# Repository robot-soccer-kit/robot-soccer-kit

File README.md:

# Robot Soccer Kit

## Presentation

* [YouTube demonstration video](https://www.youtube.com/watch?v=4NFXbaom7YQ)
* [Documentation](https://robot-soccer-kit.github.io)

The changes of each version are listed in [CHANGELOG.md](CHANGELOG.md).

## Installation

Python 3.9 or newer is required. The Game Controller (interface, vision, referee) needs the `gc`
extra:

```
pip install -U "robot-soccer-kit[gc]"
```

Only the client (to program the robots from Python) is installed without the extra:
`pip install -U robot-soccer-kit`.

**Windows**: double-click `game-controller.bat`. It installs (or updates) the package and starts
the Game Controller. It uses the `py` launcher, installed with Python from
[python.org](https://www.python.org/downloads/) (the Python of the Microsoft Store doesn't have
it).

## Game Controller

```
python -m rsk.game_controller
```

The interface opens in the browser at http://127.0.0.1:7070. Options:

| Option | Effect |
|---|---|
| `-s`, `--simulated` | Simulated robots and ball, no camera needed |
| `-c`, `--competition` | Competition mode |
| `-S URL`, `--scheduler URL` | Games of a scheduler |
| `-R FILE`, `--replay FILE` | Replay a recorded game |
| `--ip IP`, `-p PORT` | Address and port of the interface |
| `-r`, `--reset` | Reset the configuration file |
| `-d`, `--dry` | Start and stop without serving the interface (installation check) |

The configuration (robots, cameras, settings) is saved in `config.json`. Robots are not saved in
simulation and replay modes, so a simulated run doesn't replace the real robots. Recorded games
are written in `rsk_recorder/`, in the directory where the Game Controller is started.

### Vision

In the **Vision** tab:

* **Camera and resolution**: a preview of the chosen camera is shown before the vision starts.
  On Linux, the cameras are listed with their names, and only the resolutions they can give
  are proposed (with their frame rate).
* **Settings per camera**: the camera settings and the lens calibration are saved for each
  camera; changing the camera brings back its settings. A camera used for the first time gets
  its own default image settings (when known, Linux).
* **Auto**: sets the image settings to the defaults of the camera, then searches the exposure
  (brightest parts of the field bright but not saturated, or a medium brightness when the
  field is not calibrated yet: run it again once the four field markers are visible).
* **Auto crop**: crops the image to the field and the border around it.
* **Lights**: 50 Hz, 60 Hz or none. With 50 or 60 Hz, the exposure is a multiple of the
  flickering period of the lights, to avoid bands on the image.
* **Lens calibration** (Camera tab): see below.

The default focal (935) is the one of the recommended camera. A configuration that still has the
previous default (885) is updated, a custom focal is kept.

### Lens calibration

Wide angle lenses distort the image: without calibration, positions near the field borders can
be wrong by 1 to 2.5 cm (a few millimeters with it). The calibration measures the focal, the optical center and the
distortion with a ChArUco board (a chessboard with ArUco markers, the size doesn't matter):

1. Download the board from the *Lens calibration* card (Vision tab), print it, glue it on a
   flat rigid support.
2. Start the calibration and move the board in front of the camera: a view is captured each
   time the board is still in a new position (a green frame is shown). At least 30 views are
   needed, and all the zones of the coverage grid must be green (bring the board in the
   corners).
3. Compute, check the result (reprojection error, focal, field of view), then apply. The focal
   setting is also set to the measured focal.

The calibration is used only at the resolution it was made with. The same calibration can be
done with a command line tool:

```
python -m rsk.calibrate_camera --generate            # writes calibration_board.png
python -m rsk.calibrate_camera --camera 0            # live calibration ('q' cancels)
python -m rsk.calibrate_camera --images "views/*.png"
```

### Windows specifics

On Windows, OpenCV doesn't give the names, the resolutions nor the ranges of the settings of the
cameras:

* the cameras are listed by index, all the resolutions are proposed;
* the exposure is the log2 of the exposure time in seconds (e.g. `-7` for 1/128 s), so it can't
  follow the flickering of the lights, and the anti-flicker of the camera is not set;
* the automatic settings only search the exposure (the defaults of the camera are unknown).

## Development

The project is managed with [uv](https://docs.astral.sh/uv/):

```
uv sync --extra gc
uv run -m rsk.game_controller -s
```

### Tests

```
uv run --extra gc --group dev pytest tests
```

The test dependencies (pytest, hypothesis, playwright) are only installed with `--group dev`.
No Game Controller should be running (the tests use the ports 7557 and 7558).

* **Interface tests** (`tests/test_ui.py`) run in a headless Chrome, or Chromium installed with
  `uv run --group dev playwright install chromium`. They are skipped without a browser.
* **Tests with real cameras** (`tests/test_cameras_hardware.py`) are skipped unless
  `RSK_TEST_CAMERAS=1`. They check the listing, resolutions, preview rate, automatic settings
  and vision with the cameras plugged in (no other program should use them). They change the
  settings of the cameras (until unplugged), not the configuration file:

  ```
  # Linux / macOS
  RSK_TEST_CAMERAS=1 uv run --extra gc --group dev pytest tests/test_cameras_hardware.py -v -s
  # Windows (PowerShell)
  $env:RSK_TEST_CAMERAS=1; uv run --extra gc --group dev pytest tests/test_cameras_hardware.py -v -s
  ```

The CI runs the tests on Linux, macOS and Windows, with Python 3.9 to 3.14.

### Other commands

```
make format   # ruff format rsk/ tests/
make test     # tests
make          # build the package (python -m build)
```

## License

<br />This work is licensed under a <a rel="license" href="http://creativecommons.org/licenses/by-nc/2.0/">Creative Commons Attribution-NonCommercial 2.0 Generic License</a>.

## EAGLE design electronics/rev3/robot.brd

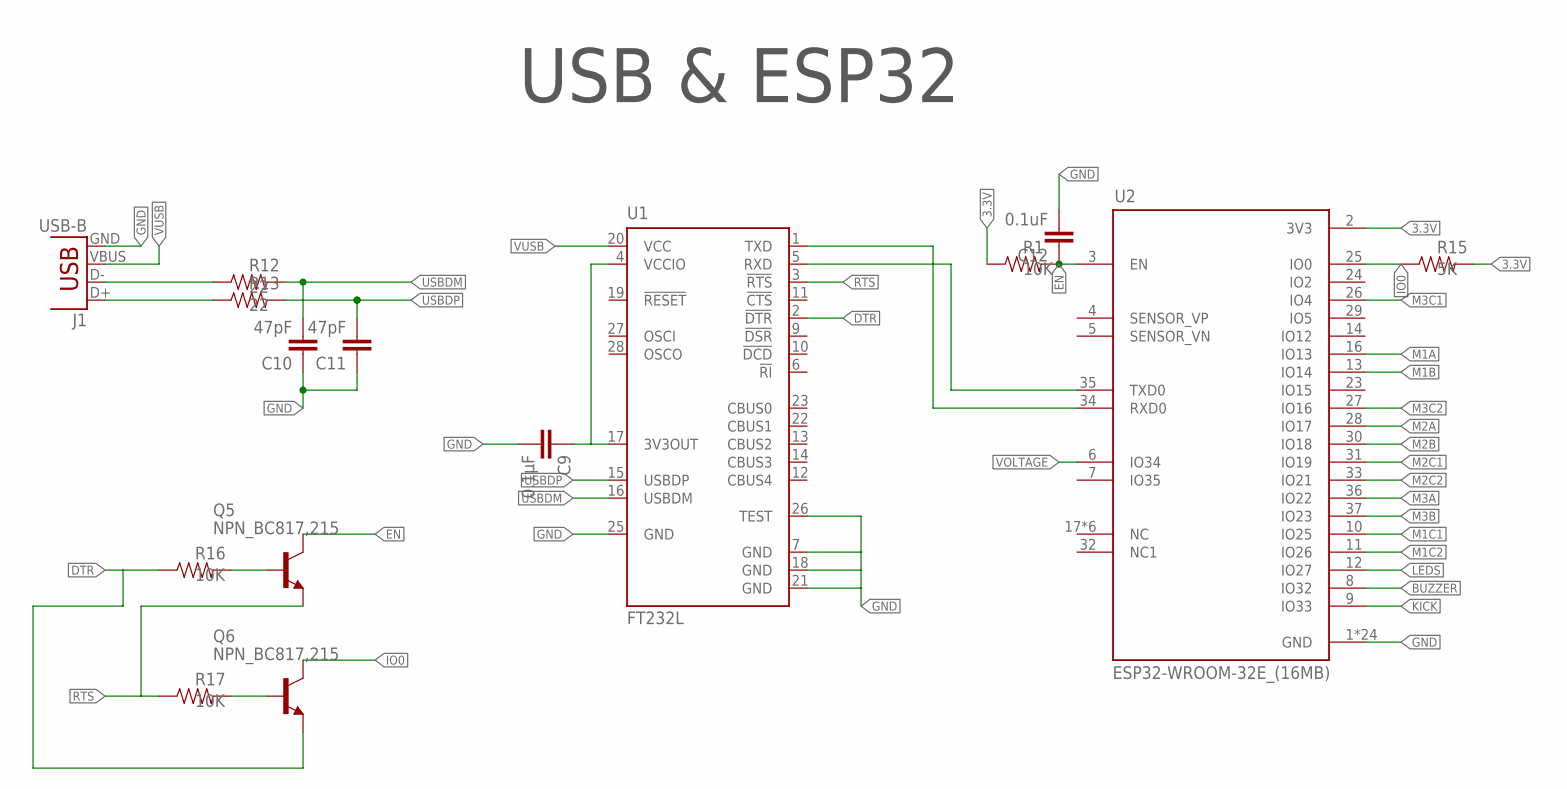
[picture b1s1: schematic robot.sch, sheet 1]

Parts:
C9: 0.1µF; 0805; FARNELL 2688486RL
C10, C11: 47pF; 0805; FARNELL 1081223
C12: 0.1uF; 0805; FARNELL 1081223
J1: USB-B; USB-B-PTH; FARNELL 1308876
Q5, Q6: NPN_BC817,215; SOT-23; FARNELL 1081223
R1, R16, R17: 10K; 0805; FARNELL 2446926
R12, R13: 22; 0805; FARNELL 2446926
R15: 5K; 0805; FARNELL 2446926
U1: FT232L; SSOP28; FARNELL 1146032
U2: ESP32-WROOM-32E_(16MB); MODULE_ESP32-WROOM-32E_(16MB); FARNELL ESP32-WROOM

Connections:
3.3V: R1.1, R15.2, U2.2 (3V3); also elsewhere on the board
BUZZER: U2.8 (IO32); also elsewhere on the board
DTR: Q6.2 (E), R16.1, U1.2 (!DTR)
EN: C12.1, Q5.3 (C), R1.2, U2.3 (EN)
GND: C9.2, C10.1, C11.1, C12.2, J1.GND, U1.7 (GND), U1.18 (GND), U1.21 (GND), U1.25 (GND), U1.26 (TEST), U2.1 (GND), U2.15 (GND), U2.38 (GND), U2.39_1 (GND), U2.39_2 (GND), U2.39_3 (GND), U2.39_4 (GND), U2.39_5 (GND), U2.39_6 (GND), U2.39_7 (GND), U2.39_8 (GND), U2.39_9 (GND), U2.39_10 (GND), U2.39_11 (GND), U2.39_12 (GND), U2.39_13 (GND), U2.39_14 (GND), U2.39_15 (GND), U2.39_16 (GND), U2.39_17 (GND), U2.39_18 (GND), U2.39_19 (GND), U2.39_20 (GND), U2.39_21 (GND); also elsewhere on the board
IO0: Q6.3 (C), R15.1, U2.25 (IO0)
KICK: U2.9 (IO33); also elsewhere on the board
LEDS: U2.12 (IO27); also elsewhere on the board
M1A: U2.16 (IO13); also elsewhere on the board
M1B: U2.13 (IO14); also elsewhere on the board
M1C1: U2.10 (IO25); also elsewhere on the board
M1C2: U2.11 (IO26); also elsewhere on the board
M2A: U2.28 (IO17); also elsewhere on the board
M2B: U2.30 (IO18); also elsewhere on the board
M2C1: U2.31 (IO19); also elsewhere on the board
M2C2: U2.33 (IO21); also elsewhere on the board
M3A: U2.36 (IO22); also elsewhere on the board
M3B: U2.37 (IO23); also elsewhere on the board
M3C1: U2.26 (IO4); also elsewhere on the board
M3C2: U2.27 (IO16); also elsewhere on the board
unnamed: U1.1 (TXD), U2.34 (RXD0)
unnamed: U1.5 (RXD), U2.35 (TXD0)
unnamed: C9.1, U1.4 (VCCIO), U1.17 (3V3OUT)
unnamed: Q5.1 (B), R16.2
unnamed: Q6.1 (B), R17.2
unnamed: J1.D-, R12.1
unnamed: J1.D+, R13.1
RTS: Q5.2 (E), R17.1, U1.3 (!RTS)
USBDM: C10.2, R12.2, U1.16 (USBDM)
USBDP: C11.2, R13.2, U1.15 (USBDP)
VOLTAGE: U2.6 (IO34); also elsewhere on the board
VUSB: J1.VBUS, U1.20 (VCC); also elsewhere on the board

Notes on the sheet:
USB & ESP32

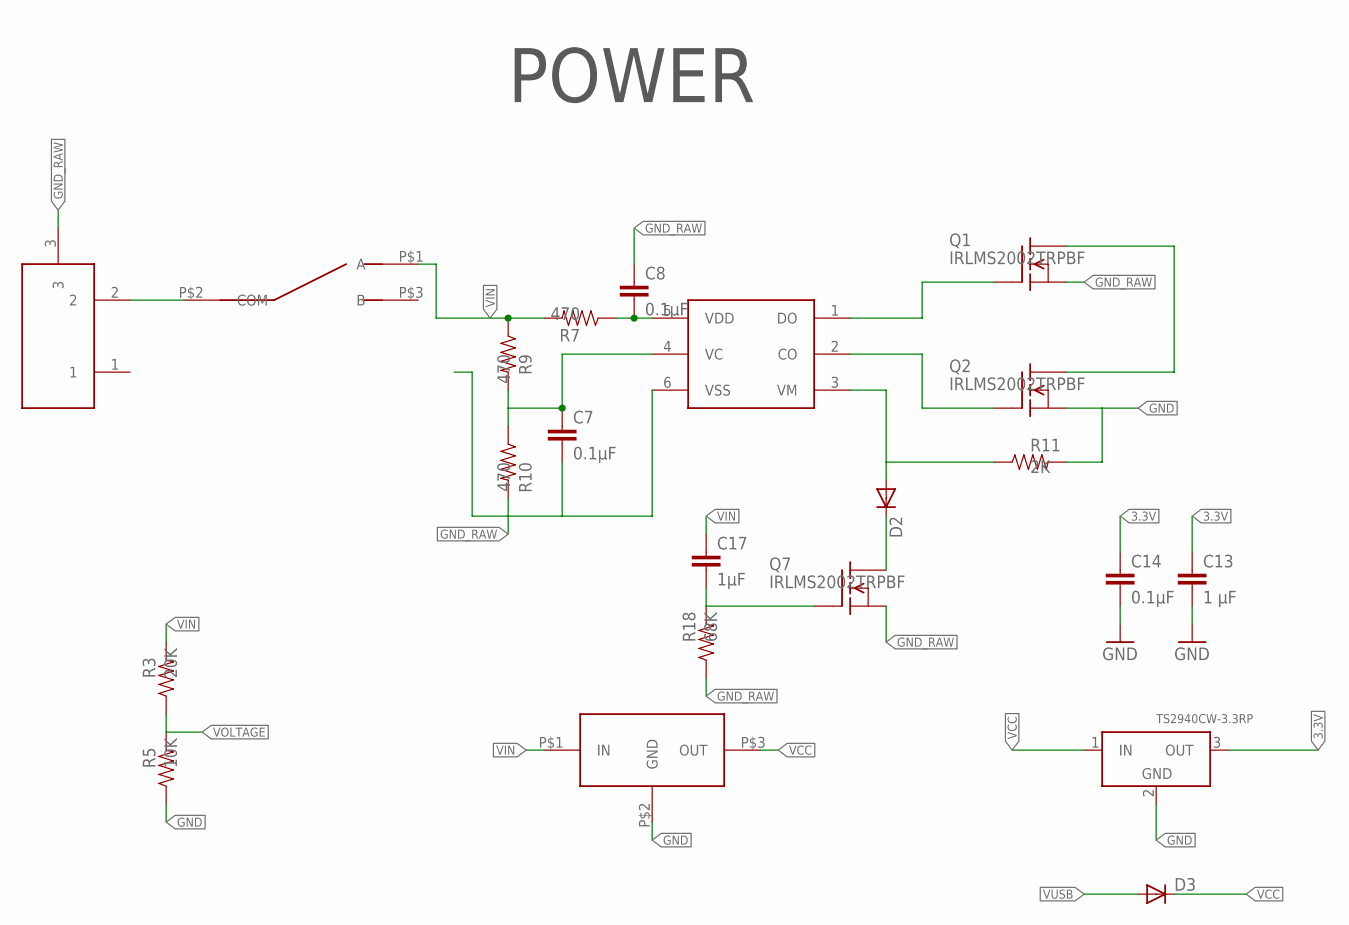
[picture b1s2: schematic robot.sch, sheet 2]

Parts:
C7, C8, C14: 0.1µF; 0805; FARNELL 2688486RL
C13: 1 µF; 0805; FARNELL 2688486RL
C17: 1µF; 0805; FARNELL 3010154
D2, D3: DIODESOD; SOD-323; FARNELL 8737843RL
J2: DC21MMX; DC-21MM; FARNELL 1217037
Q1, Q2, Q7: IRLMS2002TRPBF; SOT23-6; FARNELL 2577180RL
R3: 20K; 0805; FARNELL 2074395
R5: 10K; 0805; FARNELL 2074334RL
R7: 470; 0805; FARNELL 2447662
R9, R10: 470; 0805; FARNELL 2074334RL
R11: 2K; 0805; FARNELL 2447622
R18: 68K; 0805; FARNELL 2074486
REG1: REG_5V; TRACOPOWER; FARNELL 1696320
SW1: L102011ML04Q
U3: S8252; SOT23-6
U8: TS2940CW-3.3RP; SOT223; FARNELL 7261403

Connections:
1: J2.1
3.3V: C13.1, C14.1, U8.3 (OUT); also elsewhere on the board
GND: C13.2, C14.2, Q2.4 (S), R5.1, R11.2, REG1.P$2 (GND), U8.2 (GND); also elsewhere on the board
GND_RAW: C7.2, C8.1, J2.3, Q1.4 (S), Q7.4 (S), R10.2, R18.1, U3.6 (VSS)
unnamed: J2.2, SW1.P$2 (COM)
unnamed: C8.2, R7.1, U3.5 (VDD)
unnamed: C7.1, R9.2, R10.1, U3.4 (VC)
unnamed: Q1.1 (D), Q1.2 (D), Q1.5 (D), Q1.6 (D), Q2.1 (D), Q2.2 (D), Q2.5 (D), Q2.6 (D)
unnamed: Q2.3 (G), U3.2 (CO)
unnamed: Q1.3 (G), U3.1 (DO)
unnamed: D2.2 (A), R11.1, U3.3 (VM)
unnamed: C17.2, Q7.3 (G), R18.2
unnamed: D2.1 (C), Q7.1 (D), Q7.2 (D), Q7.5 (D), Q7.6 (D)
VCC: D3.1 (C), REG1.P$3 (OUT), U8.1 (IN); also elsewhere on the board
VIN: C17.1, R3.2, R7.2, R9.1, REG1.P$1 (IN), SW1.P$1 (A); also elsewhere on the board
VOLTAGE: R3.1, R5.2; also elsewhere on the board
VUSB: D3.2 (A); also elsewhere on the board

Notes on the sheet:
POWER

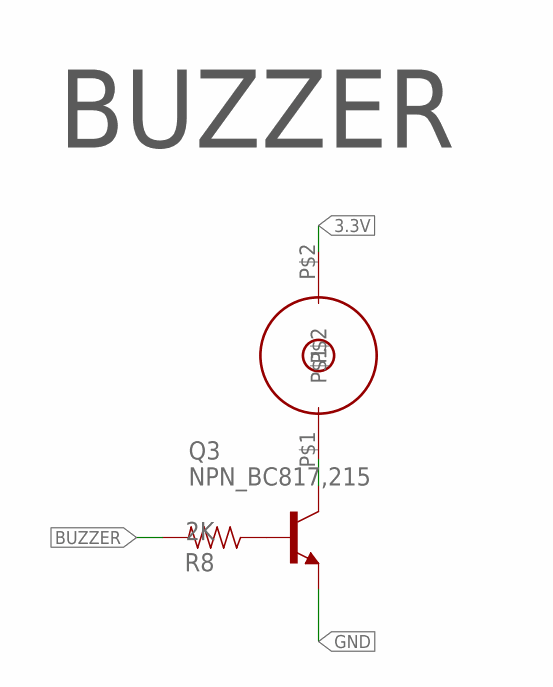
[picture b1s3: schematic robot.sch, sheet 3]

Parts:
B1: BUZZER66; FARNELL CEM-1203
Q3: NPN_BC817,215; SOT-23; FARNELL 1081223
R8: 2K; 0805; FARNELL 2447622

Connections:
3.3V: B1.P$2; also elsewhere on the board
BUZZER: R8.2; also elsewhere on the board
GND: Q3.2 (E); also elsewhere on the board
unnamed: Q3.1 (B), R8.1
unnamed: B1.P$1, Q3.3 (C)

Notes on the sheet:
BUZZER

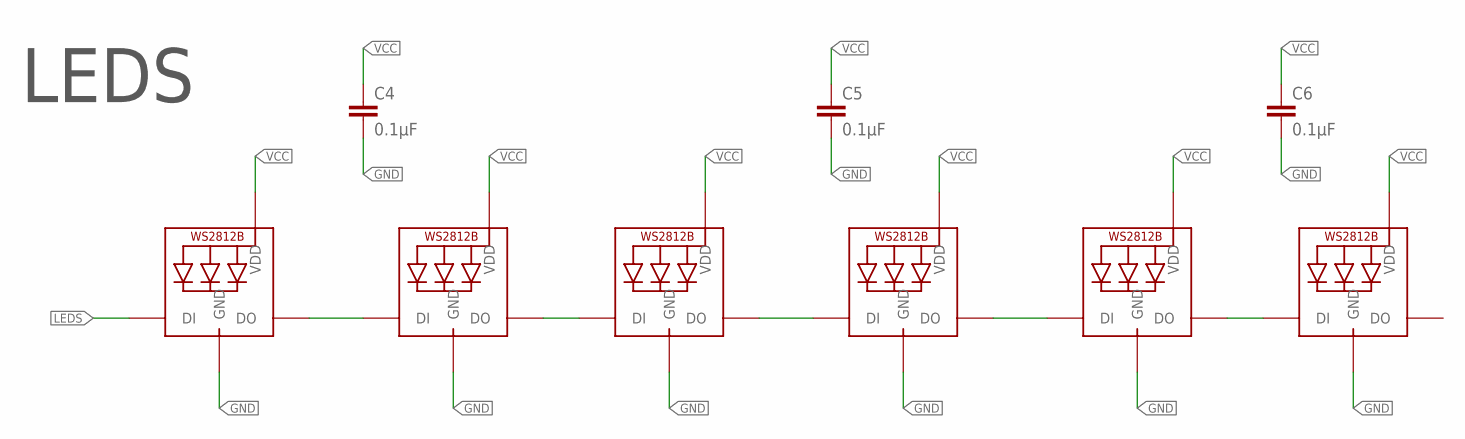
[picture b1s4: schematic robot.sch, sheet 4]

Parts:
C4, C5, C6: 0.1µF; 0805; FARNELL 2688486RL
LED1, LED2, LED3, LED4, LED5, LED6: WS2812B5050; WS2812B; FARNELL WS2812B 5050

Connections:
GND: C4.2, C5.2, C6.2, LED1.3-GND (GND), LED2.3-GND (GND), LED3.3-GND (GND), LED4.3-GND (GND), LED5.3-GND (GND), LED6.3-GND (GND); also elsewhere on the board
LEDS: LED1.4-DIN (DI); also elsewhere on the board
unnamed: LED1.2-DOUT (DO), LED2.4-DIN (DI)
unnamed: LED2.2-DOUT (DO), LED3.4-DIN (DI)
unnamed: LED4.2-DOUT (DO), LED5.4-DIN (DI)
unnamed: LED5.2-DOUT (DO), LED6.4-DIN (DI)
unnamed: LED3.2-DOUT (DO), LED4.4-DIN (DI)
VCC: C4.1, C5.1, C6.1, LED1.1-VDD (VDD), LED2.1-VDD (VDD), LED3.1-VDD (VDD), LED4.1-VDD (VDD), LED5.1-VDD (VDD), LED6.1-VDD (VDD); also elsewhere on the board

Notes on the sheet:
LEDS

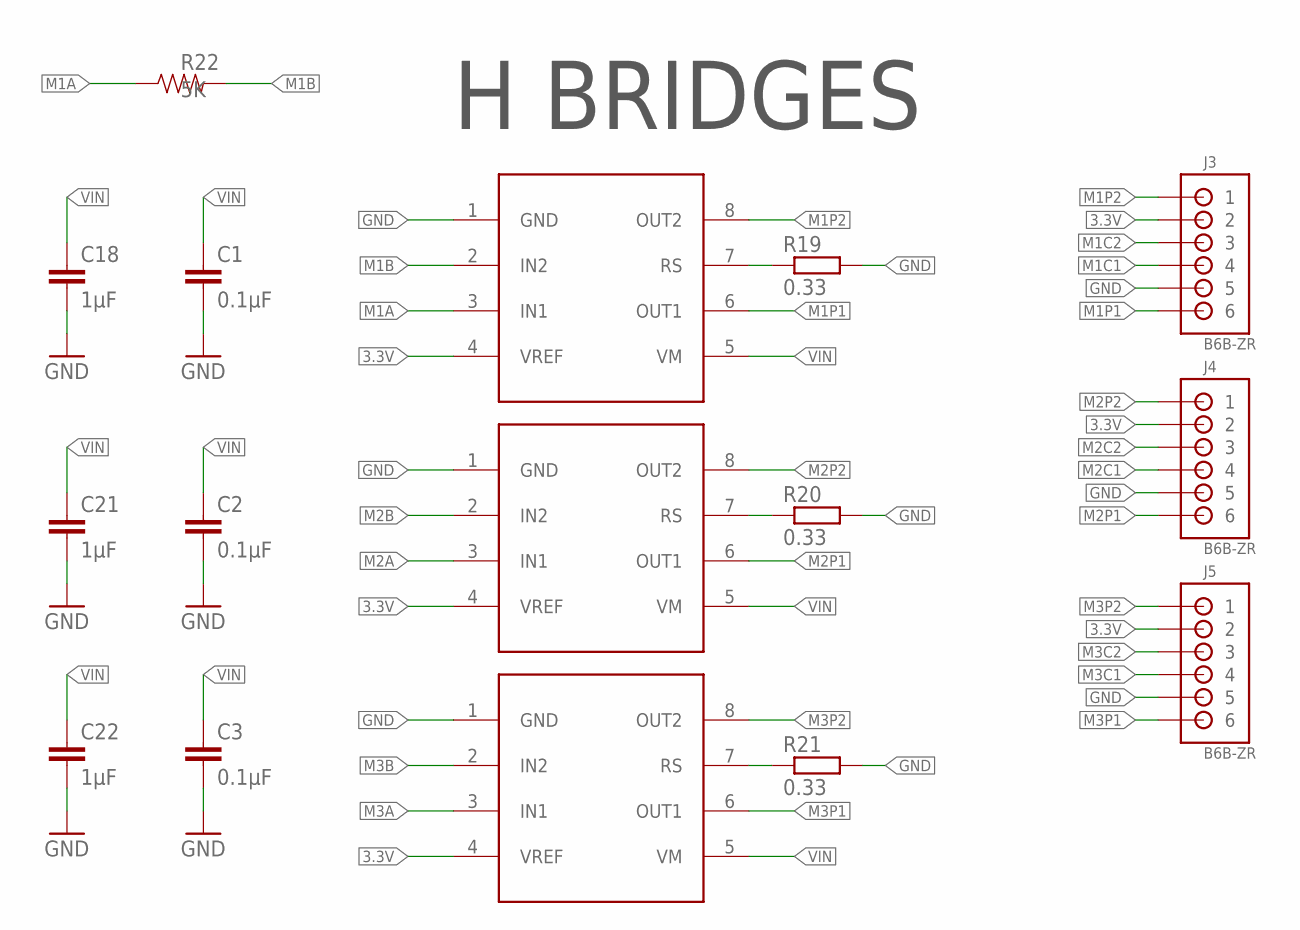
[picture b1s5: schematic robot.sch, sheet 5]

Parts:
C1, C2, C3: 0.1µF; 0805; FARNELL 2688486RL
C18, C21, C22: 1µF; 0805; FARNELL 2688486RL
J3, J4, J5: B6B-ZR; FARNELL 9491805
R19, R20, R21: 0.33; R1206
R22: 5K; 0805; FARNELL 2446926
U10, U11, U12: TB67H450FNG; HSOP8

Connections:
3.3V: J3.2, J4.2, J5.2, U10.4 (VREF), U11.4 (VREF), U12.4 (VREF); also elsewhere on the board
GND: C1.2, C2.2, C3.2, C18.2, C21.2, C22.2, J3.5, J4.5, J5.5, R19.2, R20.2, R21.2, U10.1 (GND), U11.1 (GND), U12.1 (GND); also elsewhere on the board
M1A: R22.1, U10.3 (IN1); also elsewhere on the board
M1B: R22.2, U10.2 (IN2); also elsewhere on the board
M1C1: J3.4; also elsewhere on the board
M1C2: J3.3; also elsewhere on the board
M1P1: J3.6, U10.6 (OUT1)
M1P2: J3.1, U10.8 (OUT2)
M2A: U11.3 (IN1); also elsewhere on the board
M2B: U11.2 (IN2); also elsewhere on the board
M2C1: J4.4; also elsewhere on the board
M2C2: J4.3; also elsewhere on the board
M2P1: J4.6, U11.6 (OUT1)
M2P2: J4.1, U11.8 (OUT2)
M3A: U12.3 (IN1); also elsewhere on the board
M3B: U12.2 (IN2); also elsewhere on the board
M3C1: J5.4; also elsewhere on the board
M3C2: J5.3; also elsewhere on the board
M3P1: J5.6, U12.6 (OUT1)
M3P2: J5.1, U12.8 (OUT2)
unnamed: R19.1, U10.7 (RS)
unnamed: R20.1, U11.7 (RS)
unnamed: R21.1, U12.7 (RS)
VIN: C1.1, C2.1, C3.1, C18.1, C21.1, C22.1, U10.5 (VM), U11.5 (VM), U12.5 (VM); also elsewhere on the board

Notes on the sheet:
H BRIDGES

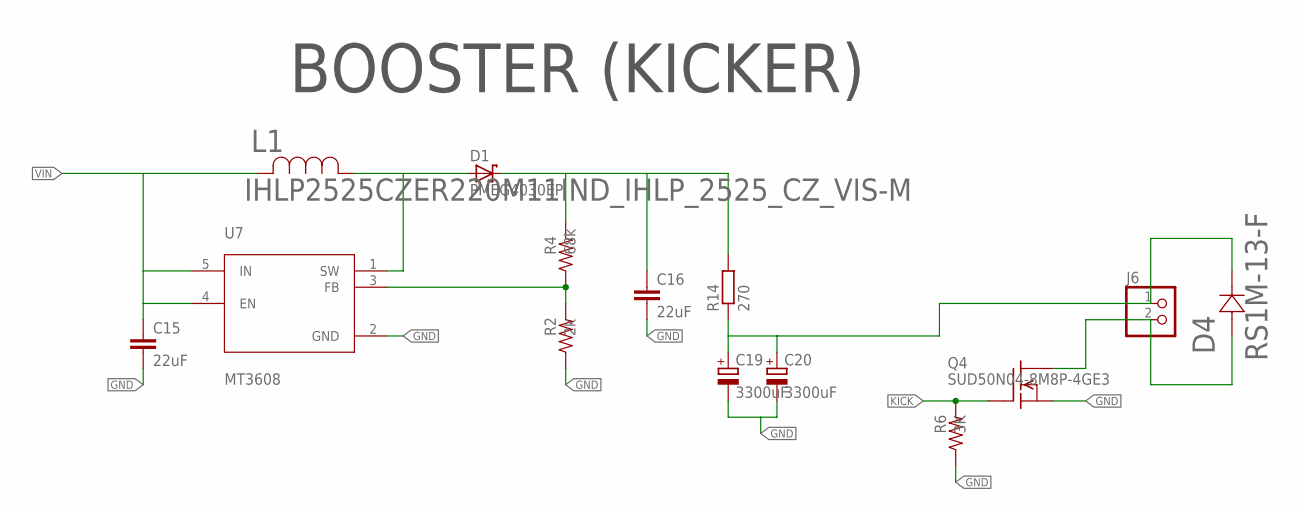
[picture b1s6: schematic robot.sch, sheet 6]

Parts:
C15, C16: 22uF; C0805; FARNELL 2666560
C19, C20: 3300uF; E5-13; MOUSER 710-860160278042
D1: PMEG4030EP; SOD128; FARNELL 1829201
D4: RS1M-13-F; RS1M
J6: RHOBAN_KICKER; FARNELL JF-0530B
L1: IHLP2525CZER220M11IND_IHLP_2525_CZ_VIS-M; IND_IHLP_2525_CZ_VIS-M; FARNELL 1741369
Q4: SUD50N04-8M8P-4GE3; TO252; FARNELL 1794799
R2: 2k; 0805; FARNELL 2447622
R4: 68k; 0805; FARNELL 2447023
R6: 3K; 0805; FARNELL 1887603
R14: 270; R2010; FARNELL 1887603
U7: MT3608; SOT95P280X145-6N; FARNELL MT3608

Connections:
GND: C15.2, C16.2, C19.-, C20.-, Q4.2 (S), R2.1, R6.1, U7.2 (GND); also elsewhere on the board
KICK: Q4.1 (G), R6.2; also elsewhere on the board
KICKER: D4.A, J6.2, Q4.3 (D)
unnamed: D1.2 (A), L1.1, U7.1 (SW)
unnamed: C16.1, D1.1 (K), R4.2, R14.2
unnamed: R2.2, R4.1, U7.3 (FB)
VIN: C15.1, L1.2, U7.4 (EN), U7.5 (IN); also elsewhere on the board
VSTORE: C19.+, C20.+, D4.K, J6.1, R14.1

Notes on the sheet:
BOOSTER (KICKER)

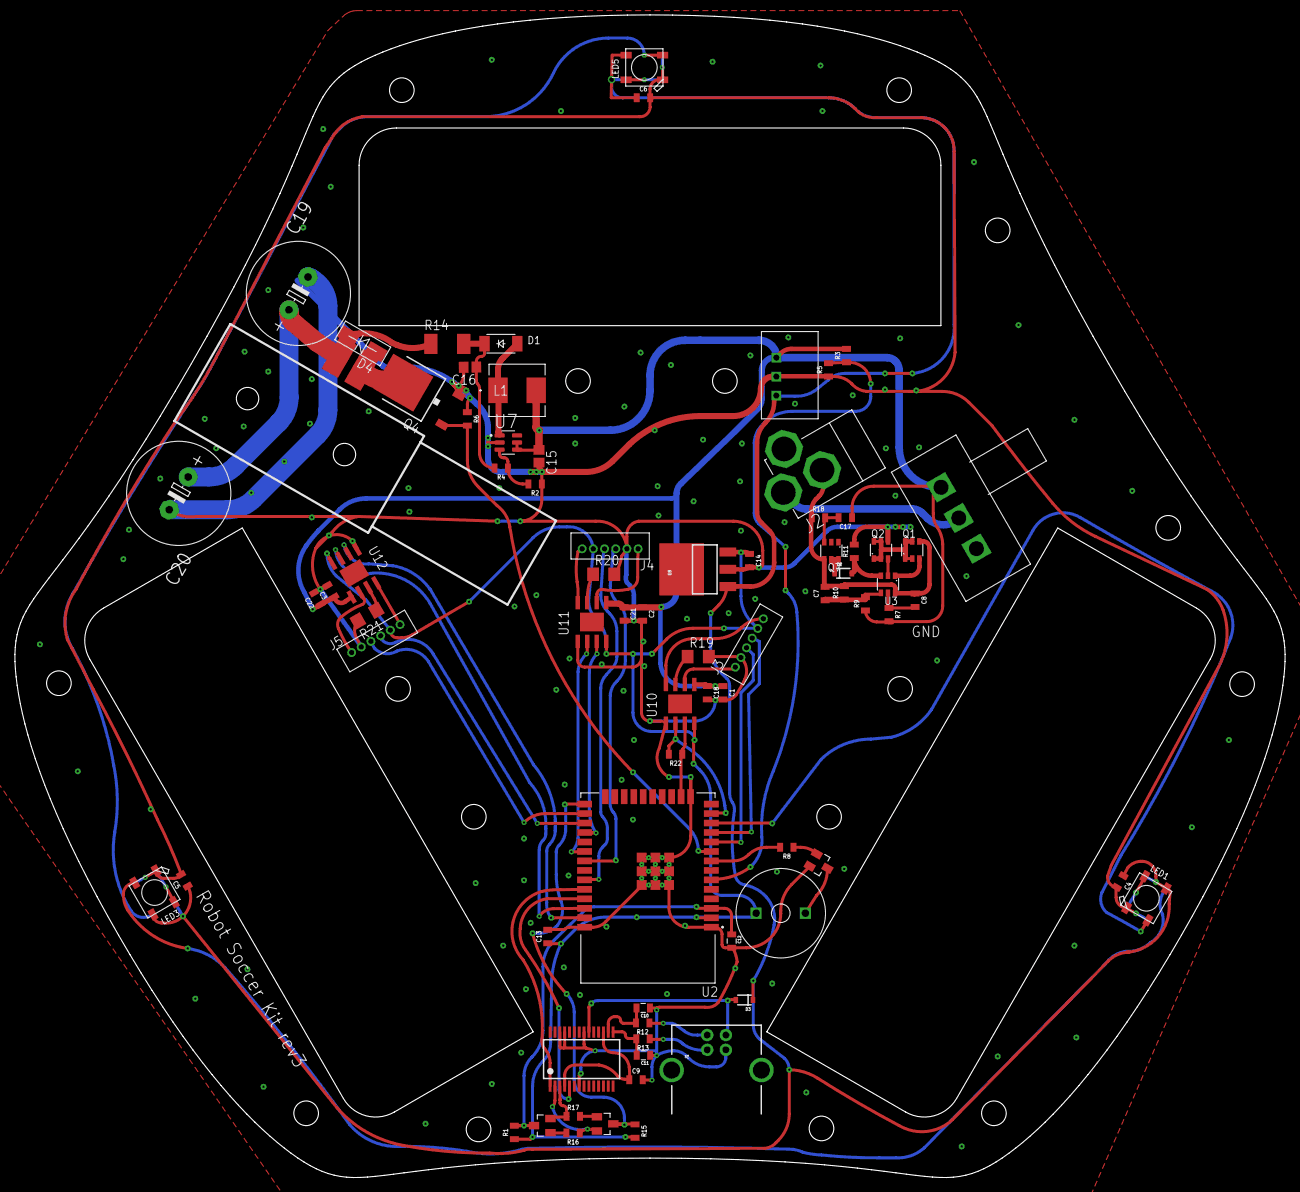
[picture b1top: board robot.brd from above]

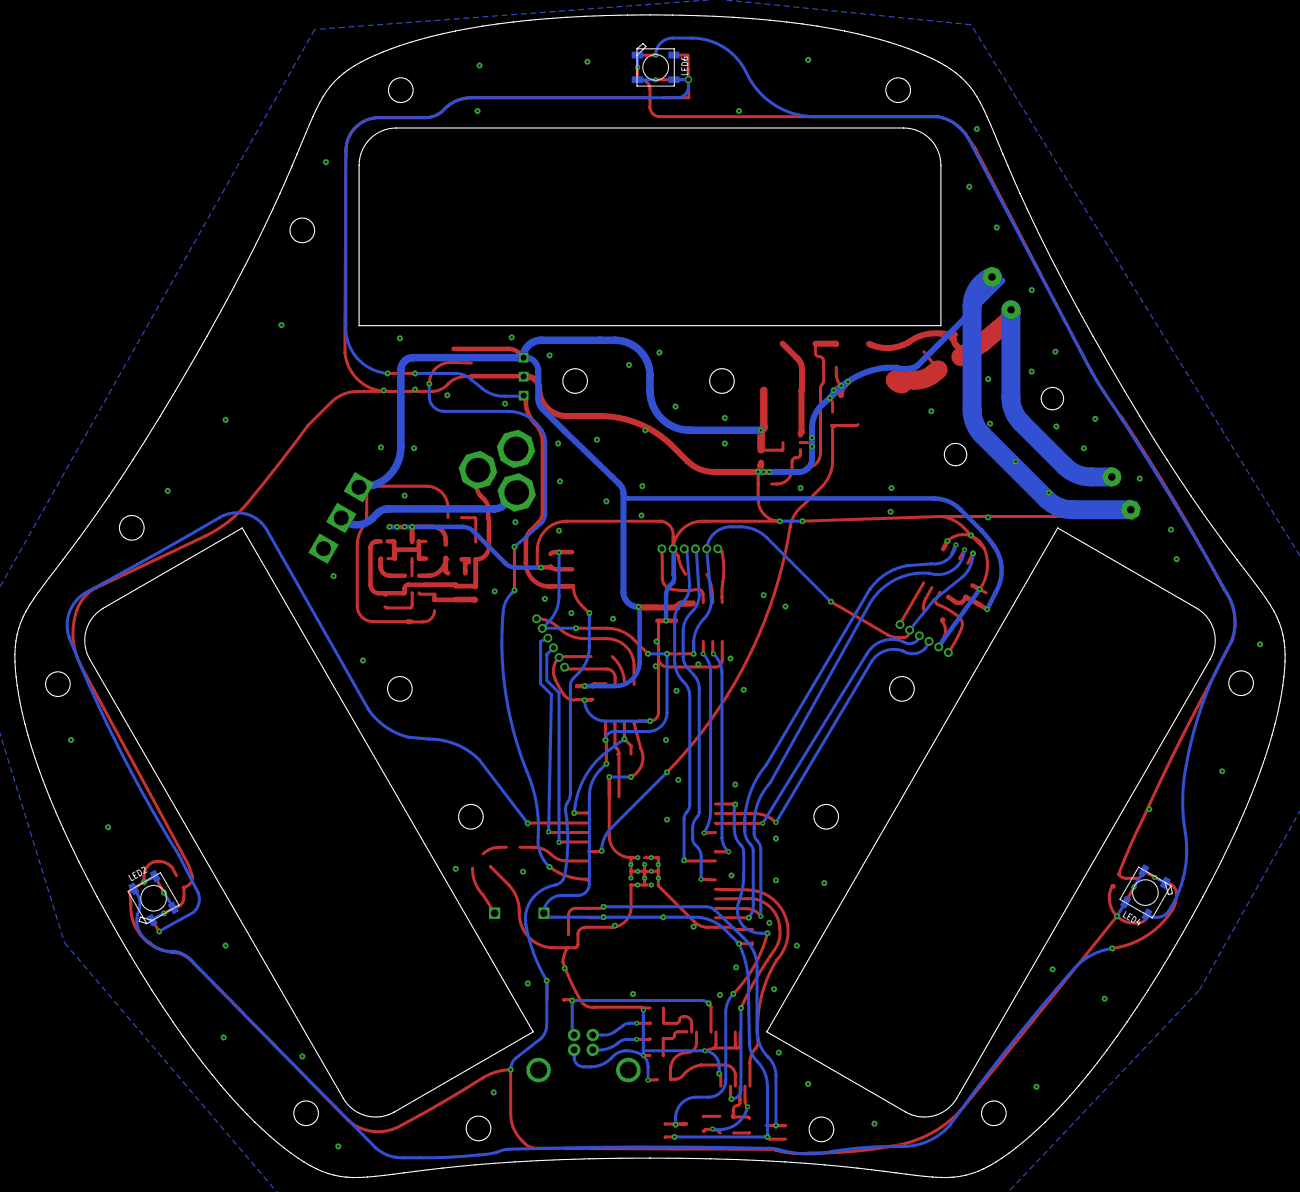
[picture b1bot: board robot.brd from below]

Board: 2 copper layers, 170.3 x 155.9 mm, 95 parts (3 on the bottom side), 65 nets.

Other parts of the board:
U$2, U$3, U$4, U$5, U$6, U$8, U$9, U$10, U$11, U$15, U$31, U$33, U$35, U$36, U$38, U$39: STAND-OFF

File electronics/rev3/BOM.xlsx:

Item # | Ref | Qty | Manufacturer | Mfg Part # | Description | Package | Type | Instruction
1 | R2 | 1 | MULTICOMP PRO | MCSR08X2001FTL | 2k ohms | R0805 | SMD
2 | R3 | 1 | MULTICOMP PRO | MCSR08X2002FTL | 20k ohms | R0805 | SMD
3 | R4, R18 | 2 | MULTICOMP PRO | MCWR08X6802FTL | 68k ohms | R0805 | SMD
4 | R1, R5, R16, R17 | 4 | MULTICOMP PRO | MCSR08X1002FTL | 10k ohms | R0805 | SMD
5 | R6 | 1 | MULTICOMP PRO | MCWR08X3001FTL | 3k ohms | R0805 | SMD
6 | R7, R9, R10 | 3 | MULTICOMP PRO | MCWR08X4700FTL | 470 ohms | R0805 | SMD
7 | R8, R11 | 2 | MULTICOMP PRO | MCWR08X2001FTL | 2k ohms | R0805 | SMD
8 | R12, R13 | 2 | MULTICOMP PRO | MCWR08X22R0FTL | 22 ohms | R0805 | SMD
9 | R15, R22 | 2 | MULTICOMP PRO | MCWR08X5101FTL | 5.1k ohms | R0805 | SMD
10 | R14 | 1 | MULTICOMP PRO | MCPWR10FTEQ2700 | Kicker resistor (270) | R2010 | SMD
11 | R19 , R20, R21 | 3 | VISHAY | RCWE0805R330FKEA | 330 mOhms | R0805 | SMD
12 | C13, C17, C18, C21, C22 | 5 | MURATA | GCM21BR71E105KA56L | 1µF | C0805 | SMD
13 | C1, C2, C3, C4, C5, C6, C7, C8, C9, C12, C14 | 11 | MURATA | GCM21BR72A104KA37K | 0.1µF | C0805 | SMD
14 | C10, C11 | 2 | MULTICOMP PRO | MC0805N470J500CT | 47pF (USB) | C0805 | SMD
15 | C15, C16 | 2 | MURATA | GRM21BR61E226ME44L | 22uF (Booster) | C0805 | SMD
16 | C19, C20 | 2 | WURTH ELEKTRONIK | 860020478022 | 2200uF 25V capacitors (Kicker) |  | Thru-holes
17 | D1 | 1 | NEXPERIA | PMEG4030EP,115 | Kicker diode | SOD-128 | SMD
18 | D2, D3 | 2 | NEXPERIA | PMEG2005AEA,115 | USB diode, BMS bootstrap polarity protection diode | SOD-323 | SMD
19 | B1 | 1 | CUI Devices | CEM-1203 | Buzzer |  | Thru-holes
20 | J1 | 1 | MULTICOMP PRO | USB-B-S-RA | USB Connector |  | Thru-holes
21 | J2 | 1 | MULTICOMP PRO | MJ-180PH | Jack 2.5mm « barrel » connector |  | Thru-holes
22 | J3, J4, J5 | 3 | JST (JAPAN SOLDERLESS TERMINALS) | B6B-ZR(LF)(SN) | JST XH 6p |  | Thru-holes
23 | J6 | 1 |  | JF-0530B | Solenoid Kicker |  | SMD | DO NOT MOUNT
24 | L1 | 1 | VISHAY | IHLP2525CZER220M11 | Kicker booster inductance |  | SMD
25 | LED1, LED2, LED3, LED4, LED5, LED6 | 6 | SparkFun | COM-16346 | RGB LEDs (WS2812B) |  | SMD
26 | Q1, Q2, Q7 | 3 | INFINEON | IRLMS2002TRPBF | BMS Mosfet |  | SMD
27 | Q3, Q5, Q6 | 3 | NEXPERIA | BC817,215 | NPN Transistor |  | SMD
28 | Q4 | 1 | MCC (MICRO COMMERCIAL COMPONENTS) | MCU60N04A-TP | Kicker MOSFET |  | SMD
29 | REG1 | 1 | TRACO POWER | TSR 1-2450E | 5V regulator (switching) |  | Thru-holes
30 | U8 | 1 | ANALOG DEVICES | LT1963AEST-3.3#PBF | 3.3V regulator (LDO) |  | SMD
31 | SW1 | 1 | C&K COMPONENTS | L102011ML04Q | Main switch (SPDT) |  | Thru-holes
32 | U1 | 1 | FTDI | FT232RL-REEL | USB 2 UART (FTDI) |  | SMD
33 | U2 | 1 | ESPRESSIF SYSTEMS | ESP32-WROOM-32E-N8 | MCU ESP32 |  | SMD
34 | U3 | 1 | ABLIC Inc. | S-8252AAL-M6T1U | BMS |  | SMD
35 | U10, U11, U12 | 3 | TOSHIBA | TB67H450FNG,EL | H-bridge | SOP8 | SMD
36 | U7 | 1 | AEROSEMI | MT3608 | Step-up Booster 20V |  | SMD
37 | CR1 | 1 | ONSEMI | RS1M | Kicker free wheel diode |  | SMD

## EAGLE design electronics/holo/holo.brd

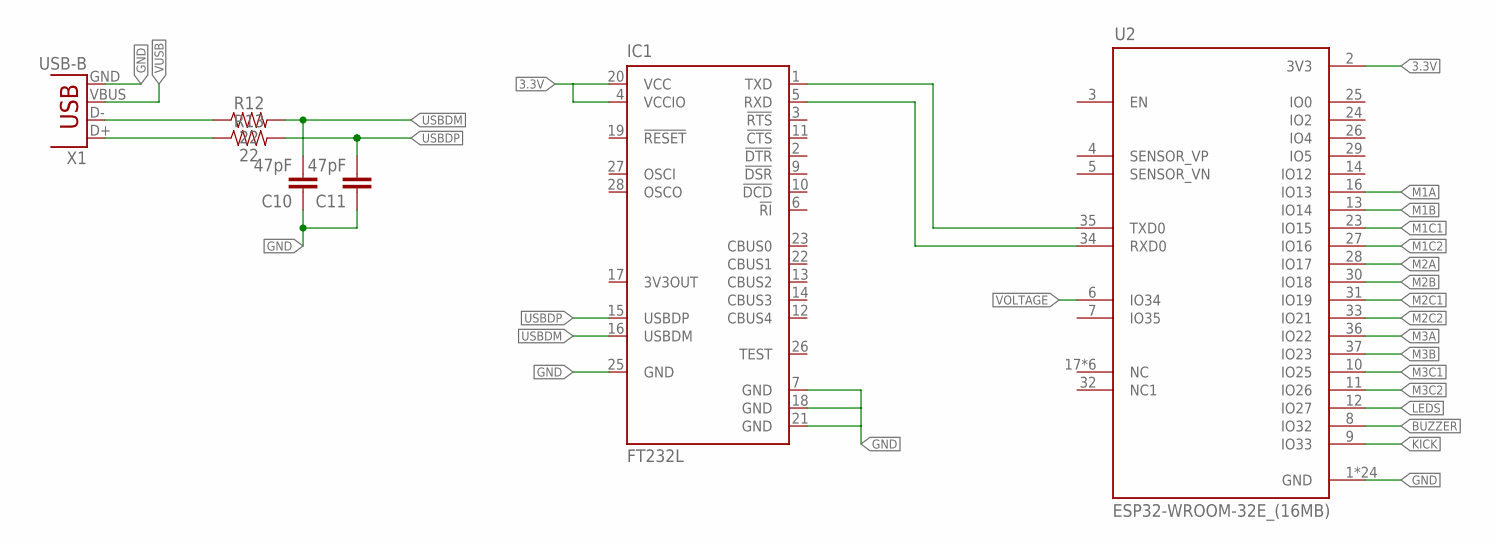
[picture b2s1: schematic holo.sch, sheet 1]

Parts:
C10, C11: 47pF; 0805; FARNELL 1081223
IC1: FT232L; SSOP28; FARNELL 1146032
R12, R13: 22; 0805; FARNELL 2446926
U2: ESP32-WROOM-32E_(16MB); MODULE_ESP32-WROOM-32E_(16MB)
X1: USB-B; USB-B-PTH; FARNELL 1308876

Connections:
3.3V: IC1.4 (VCCIO), IC1.20 (VCC), U2.2 (3V3); also elsewhere on the board
BUZZER: U2.8 (IO32); also elsewhere on the board
GND: C10.1, C11.1, IC1.7 (GND), IC1.18 (GND), IC1.21 (GND), IC1.25 (GND), U2.1 (GND), U2.15 (GND), U2.38 (GND), U2.39_1 (GND), U2.39_2 (GND), U2.39_3 (GND), U2.39_4 (GND), U2.39_5 (GND), U2.39_6 (GND), U2.39_7 (GND), U2.39_8 (GND), U2.39_9 (GND), U2.39_10 (GND), U2.39_11 (GND), U2.39_12 (GND), U2.39_13 (GND), U2.39_14 (GND), U2.39_15 (GND), U2.39_16 (GND), U2.39_17 (GND), U2.39_18 (GND), U2.39_19 (GND), U2.39_20 (GND), U2.39_21 (GND), X1.GND; also elsewhere on the board
KICK: U2.9 (IO33); also elsewhere on the board
LEDS: U2.12 (IO27); also elsewhere on the board
M1A: U2.16 (IO13); also elsewhere on the board
M1B: U2.13 (IO14); also elsewhere on the board
M1C1: U2.23 (IO15); also elsewhere on the board
M1C2: U2.27 (IO16); also elsewhere on the board
M2A: U2.28 (IO17); also elsewhere on the board
M2B: U2.30 (IO18); also elsewhere on the board
M2C1: U2.31 (IO19); also elsewhere on the board
M2C2: U2.33 (IO21); also elsewhere on the board
M3A: U2.36 (IO22); also elsewhere on the board
M3B: U2.37 (IO23); also elsewhere on the board
M3C1: U2.10 (IO25); also elsewhere on the board
M3C2: U2.11 (IO26); also elsewhere on the board
unnamed: IC1.1 (TXD), U2.35 (TXD0)
unnamed: IC1.5 (RXD), U2.34 (RXD0)
unnamed: R12.1, X1.D-
unnamed: R13.1, X1.D+
USBDM: C10.2, IC1.16 (USBDM), R12.2
USBDP: C11.2, IC1.15 (USBDP), R13.2
VOLTAGE: U2.6 (IO34); also elsewhere on the board
VUSB: X1.VBUS; also elsewhere on the board

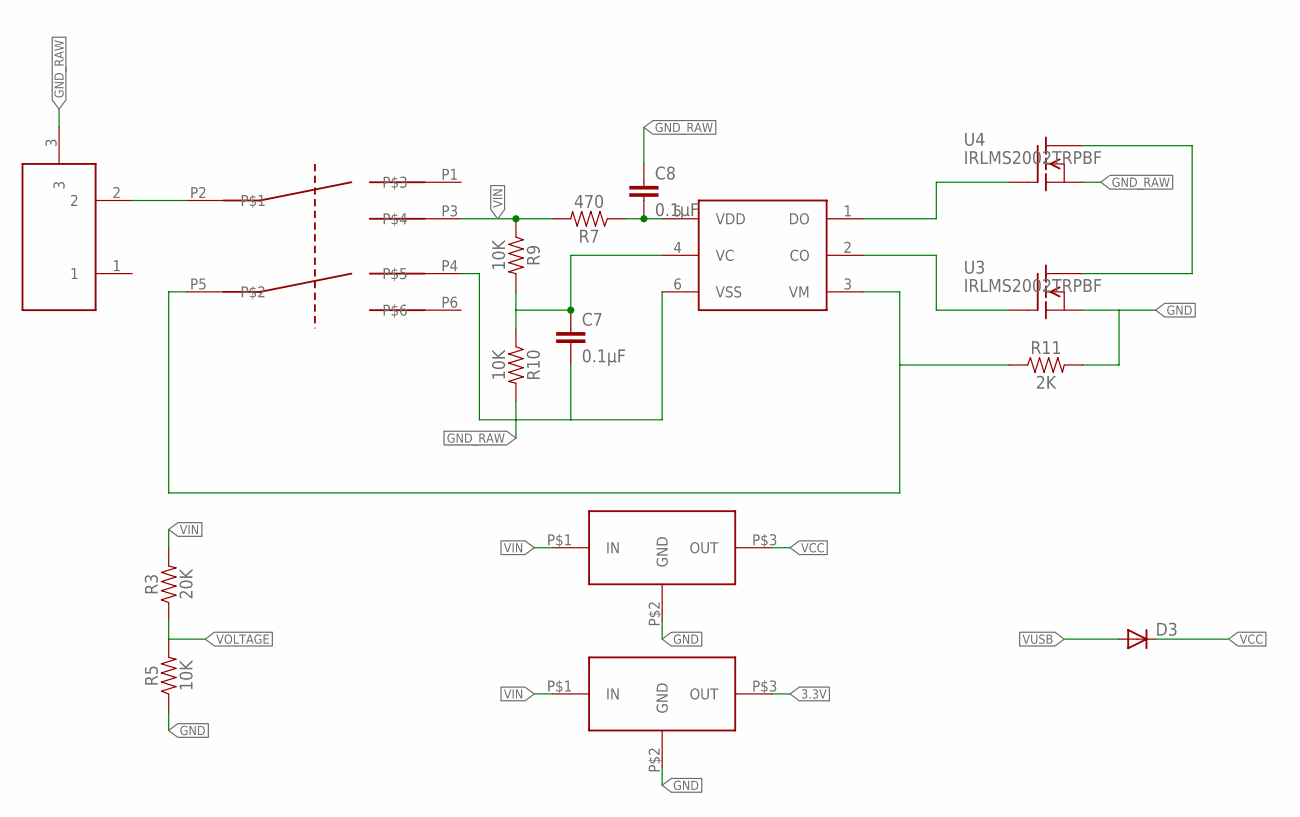
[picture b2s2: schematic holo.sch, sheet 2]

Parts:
C7, C8: 0.1µF; 0805; FARNELL 2688486RL
D3: DIODESOD; SOD-323; FARNELL 8737843RL
R3: 20K; 0805; FARNELL 2074395
R5, R9, R10: 10K; 0805; FARNELL 2074334RL
R7: 470; 0805; FARNELL 2447662
R11: 2K; 0805; FARNELL 2447622
REG, REG1: REG_5V; TRACOPOWER; FARNELL 1696320
U3, U4: IRLMS2002TRPBF; SOT23-6; FARNELL 2577180RL
U$7: S8252; SOT23-6
U$14: DPDT; L202021MA04Q; FARNELL 2435159
X2: DC21MMX; DC-21MM; FARNELL 1217037

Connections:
1: X2.1
3.3V: REG1.P$3 (OUT); also elsewhere on the board
GND: R5.1, R11.2, REG.P$2 (GND), REG1.P$2 (GND), U3.4 (S); also elsewhere on the board
GND_RAW: C7.2, C8.1, R10.2, U4.4 (S), U$7.6 (VSS), U$14.P4, X2.3
unnamed: U$14.P2, X2.2
unnamed: C8.2, R7.1, U$7.5 (VDD)
unnamed: C7.1, R9.2, R10.1, U$7.4 (VC)
unnamed: U3.1 (D), U3.2 (D), U3.5 (D), U3.6 (D), U4.1 (D), U4.2 (D), U4.5 (D), U4.6 (D)
unnamed: U3.3 (G), U$7.2 (CO)
unnamed: U4.3 (G), U$7.1 (DO)
unnamed: R11.1, U$7.3 (VM), U$14.P5
VCC: D3.1 (C), REG.P$3 (OUT); also elsewhere on the board
VIN: R3.2, R7.2, R9.1, REG.P$1 (IN), REG1.P$1 (IN), U$14.P3; also elsewhere on the board
VOLTAGE: R3.1, R5.2; also elsewhere on the board
VUSB: D3.2 (A); also elsewhere on the board

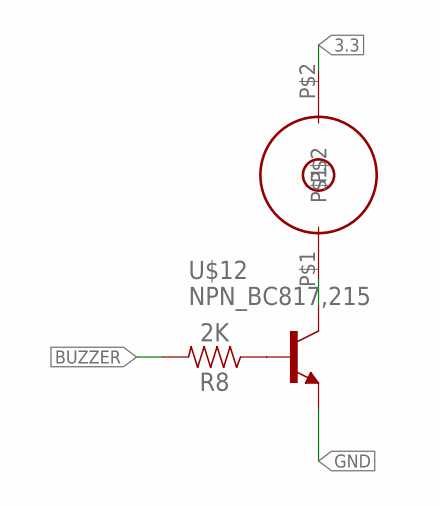
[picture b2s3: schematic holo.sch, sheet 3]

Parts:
R8: 2K; 0805; FARNELL 2447622
U$12: NPN_BC817,215; SOT-23; FARNELL 1081223
U$13: BUZZER66; FARNELL CEM-1203

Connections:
3.3: U$13.P$2; also elsewhere on the board
BUZZER: R8.2; also elsewhere on the board
GND: U$12.2 (E); also elsewhere on the board
unnamed: R8.1, U$12.1 (B)
unnamed: U$12.3 (C), U$13.P$1

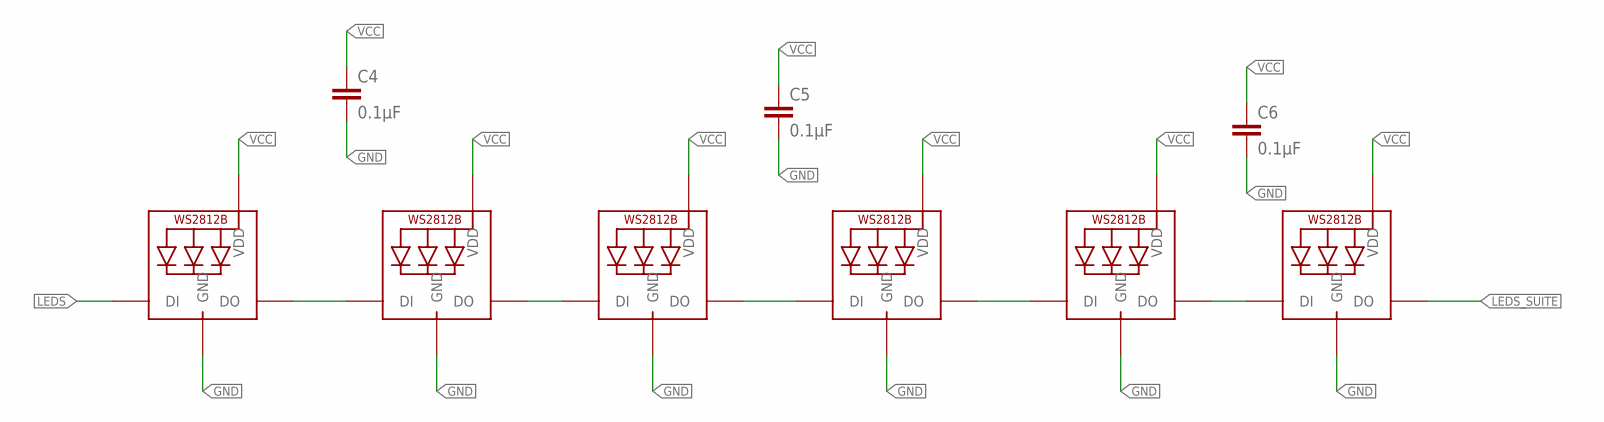
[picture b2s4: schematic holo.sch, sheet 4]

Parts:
C4, C5, C6: 0.1µF; 0805; FARNELL 2688486RL
LED1, LED2, LED3, LED4, LED5, LED6: WS2812B5050; WS2812B; FARNELL WS2812B 5050

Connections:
GND: C4.2, C5.2, C6.2, LED1.3-GND (GND), LED2.3-GND (GND), LED3.3-GND (GND), LED4.3-GND (GND), LED5.3-GND (GND), LED6.3-GND (GND); also elsewhere on the board
LEDS: LED1.4-DIN (DI); also elsewhere on the board
LEDS_SUITE: LED6.2-DOUT (DO)
unnamed: LED1.2-DOUT (DO), LED2.4-DIN (DI)
unnamed: LED2.2-DOUT (DO), LED3.4-DIN (DI)
unnamed: LED4.2-DOUT (DO), LED5.4-DIN (DI)
unnamed: LED5.2-DOUT (DO), LED6.4-DIN (DI)
unnamed: LED3.2-DOUT (DO), LED4.4-DIN (DI)
VCC: C4.1, C5.1, C6.1, LED1.1-VDD (VDD), LED2.1-VDD (VDD), LED3.1-VDD (VDD), LED4.1-VDD (VDD), LED5.1-VDD (VDD), LED6.1-VDD (VDD); also elsewhere on the board

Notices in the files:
parts and their libraries:
SparkFun-Electromechanical: Licensing: Creative Commons ShareAlike 4.0 International - https://creativecommons.org/licenses/by-sa/4.0
SparkFun-Passives: Licensing: CC v3.0 Share-Alike You are welcome to use this library for commercial purposes.
